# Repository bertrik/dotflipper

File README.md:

# dotflipper
My Flip Dot controller, based on the PCA9865 i2c port expanders

CC BY-SA 4.0

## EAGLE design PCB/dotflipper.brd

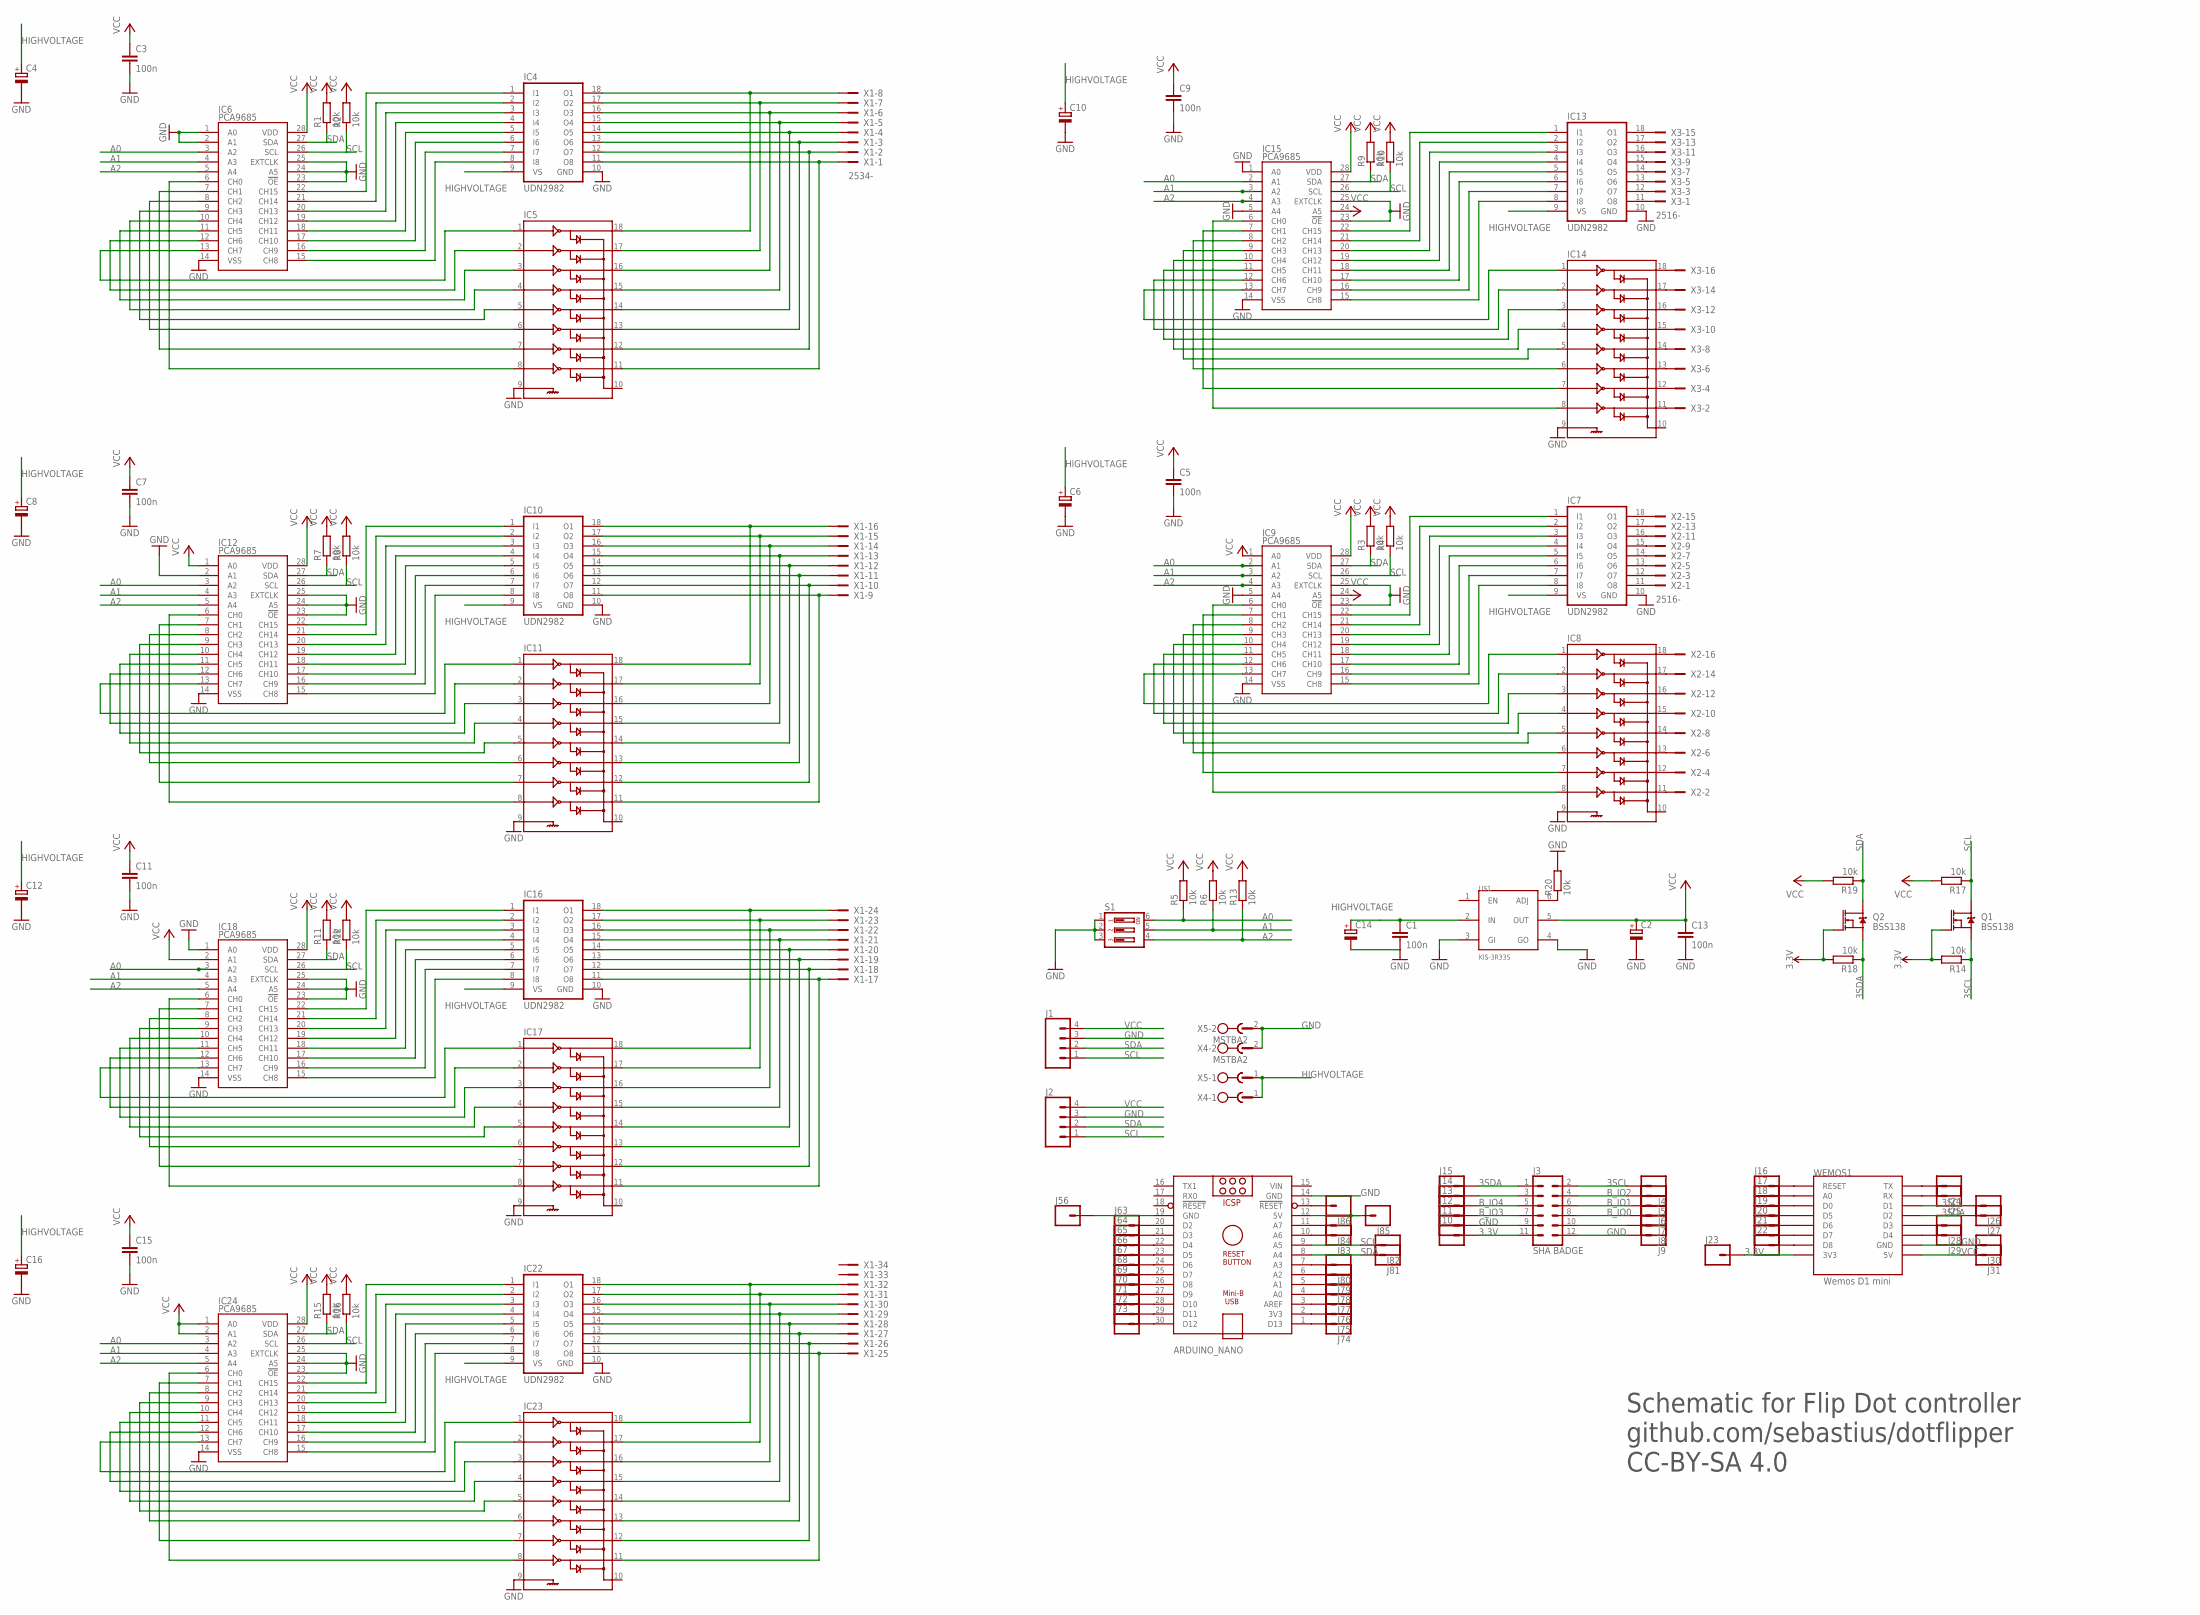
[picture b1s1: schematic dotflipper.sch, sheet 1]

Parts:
ARDUINO_NANO: ARDUINO_NANO
C1, C3, C5, C7, C9, C11, C13, C15: 100n; C0603
C2, C14: CPOL-EUSANYO_SMD_F8; SANYO-OSCON_SMD_F8
C4, C6, C8, C10, C12, C16: CPOL-EUE2.5-6; E2,5-6
IC4, IC7, IC10, IC13, IC16, IC22: UDN2982; DIL18
IC5, IC8, IC11, IC14, IC17, IC23: ULN2803DIP; DIL18
IC6, IC9, IC12, IC15, IC18, IC24: PCA9685; TSSOP-28_4MM
J1, J2: CONN_04; 1X04
J3: SHA BADGE; 2X6
J4, J5, J6, J7, J8, J9, J10, J11, J12, J13, J14, J15, J16, J17, J18, J19, J20, J21, J22, J23, J24, J25, J26, J27, J28, J29, J30, J31, J56, J63, J64, J65, J66, J67, J68, J69, J70, J71, J72, J73, J74, J75, J76, J77, J78, J79, J80, J81, J82, J83, J84, J85, J86: CONN_01; 1X01
Q1, Q2: BSS138; SOT23-3
R1, R2, R3, R4, R5, R6, R7, R8, R9, R10, R11, R12, R13, R14, R15, R16, R17, R18, R19, R20: 10k; R0603
S1: DIP03YL
U$1: KIS-3R33S
WEMOS1: Wemos D1 mini; WEMOS-D1-MINI
X1: 2534-; PAK100/2500-34
X2, X3: 2516-; PAK100/2500-16
X4, X5: MSTBA2

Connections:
3.3V: J3.11, J10.1, J23.1, Q1.1 (G), Q2.1 (G), R14.2, R18.2, WEMOS1.3V3
3SCL: J3.2, J4.1, J26.1, Q1.2 (S), R14.1, WEMOS1.D1
3SDA: J3.1, J15.1, J27.1, Q2.2 (S), R18.1, WEMOS1.D2
A0: IC6.3 (A2), IC9.2 (A1), IC12.3 (A2), IC15.2 (A1), IC18.3 (A2), IC24.3 (A2), R5.1, S1.6
A1: IC6.4 (A3), IC9.3 (A2), IC12.4 (A3), IC15.3 (A2), IC18.4 (A3), IC24.4 (A3), R6.1, S1.5
A2: IC6.5 (A4), IC9.4 (A3), IC12.5 (A4), IC15.4 (A3), IC18.5 (A4), IC24.5 (A4), R13.1, S1.4
B_IO0: J3.8, J7.1
B_IO1: J3.6, J6.1
B_IO2: J3.4, J5.1
B_IO3: J3.7, J12.1
B_IO4: J3.5, J13.1
GND: ARDUINO_NANO.14 (GND), ARDUINO_NANO.19 (GND), C1.2, C2.-, C3.2, C4.-, C5.2, C6.-, C7.2, C8.-, C9.2, C10.-, C11.2, C12.-, C13.2, C14.-, C15.2, C16.-, IC4.10 (GND), IC5.9, IC6.1 (A0), IC6.2 (A1), IC6.14 (VSS), IC6.23 (!OE), IC6.24 (A5), IC6.25 (EXTCLK), IC7.10 (GND), IC8.9, IC9.5 (A4), IC9.14 (VSS), IC9.23 (!OE), IC9.25 (EXTCLK), IC10.10 (GND), IC11.9, IC12.2 (A1), IC12.14 (VSS), IC12.23 (!OE), IC12.24 (A5), IC12.25 (EXTCLK), IC13.10 (GND), IC14.9, IC15.1 (A0), IC15.5 (A4), IC15.14 (VSS), IC15.23 (!OE), IC15.25 (EXTCLK), IC16.10 (GND), IC17.9, IC18.1 (A0), IC18.14 (VSS), IC18.23 (!OE), IC18.24 (A5), IC18.25 (EXTCLK), IC22.10 (GND), IC23.9, IC24.14 (VSS), IC24.23 (!OE), IC24.24 (A5), IC24.25 (EXTCLK), J1.3, J2.3, J3.9, J3.12, J9.1, J11.1, J30.1, J56.1, R20.2, S1.1, S1.2, S1.3, U$1.3 (GI), U$1.4 (GO), WEMOS1.GND, X4.2, X5.2
HIGHVOLTAGE: C1.1, C4.+, C6.+, C8.+, C10.+, C12.+, C14.+, C16.+, IC4.9 (VS), IC7.9 (VS), IC10.9 (VS), IC13.9 (VS), IC16.9 (VS), IC22.9 (VS), U$1.2 (IN), X4.1, X5.1
unnamed: IC4.1 (I1), IC6.22 (CH15)
unnamed: IC4.2 (I2), IC6.21 (CH14)
unnamed: IC4.3 (I3), IC6.20 (CH13)
unnamed: IC4.4 (I4), IC6.19 (CH12)
unnamed: IC7.11 (O8), X2.1
unnamed: IC4.5 (I5), IC6.18 (CH11)
unnamed: IC8.11, X2.2
unnamed: IC7.12 (O7), X2.3
unnamed: IC8.12, X2.4
unnamed: IC7.13 (O6), X2.5
unnamed: IC7.14 (O5), X2.7
unnamed: IC7.15 (O4), X2.9
unnamed: IC7.16 (O3), X2.11
unnamed: IC7.17 (O2), X2.13
unnamed: IC7.18 (O1), X2.15
unnamed: IC8.13, X2.6
unnamed: IC4.6 (I6), IC6.17 (CH10)
unnamed: IC4.7 (I7), IC6.16 (CH9)
unnamed: IC8.14, X2.8
unnamed: IC4.8 (I8), IC6.15 (CH8)
unnamed: IC5.4, IC6.10 (CH4)
unnamed: IC8.15, X2.10
unnamed: IC8.16, X2.12
unnamed: IC8.17, X2.14
unnamed: IC5.6, IC6.8 (CH2)
unnamed: IC5.7, IC6.7 (CH1)
unnamed: IC8.18, X2.16
unnamed: IC5.8, IC6.6 (CH0)
unnamed: IC5.2, IC6.12 (CH6)
unnamed: IC5.3, IC6.11 (CH5)
unnamed: IC5.5, IC6.9 (CH3)
unnamed: IC5.1, IC6.13 (CH7)
unnamed: IC13.11 (O8), X3.1
unnamed: IC4.12 (O7), IC5.12, X1.2
unnamed: IC13.12 (O7), X3.3
unnamed: IC4.14 (O5), IC5.14, X1.4
unnamed: IC13.13 (O6), X3.5
unnamed: IC4.16 (O3), IC5.16, X1.6
unnamed: IC13.14 (O5), X3.7
unnamed: IC13.15 (O4), X3.9
unnamed: IC4.18 (O1), IC5.18, X1.8
unnamed: IC13.16 (O3), X3.11
unnamed: IC4.11 (O8), IC5.11, X1.1
unnamed: IC13.17 (O2), X3.13
unnamed: IC4.13 (O6), IC5.13, X1.3
unnamed: IC13.18 (O1), X3.15
unnamed: IC4.15 (O4), IC5.15, X1.5
unnamed: IC4.17 (O2), IC5.17, X1.7
unnamed: IC7.1 (I1), IC9.22 (CH15)
unnamed: IC7.2 (I2), IC9.21 (CH14)
unnamed: IC7.3 (I3), IC9.20 (CH13)
unnamed: IC7.4 (I4), IC9.19 (CH12)
unnamed: IC7.5 (I5), IC9.18 (CH11)
unnamed: IC7.6 (I6), IC9.17 (CH10)
unnamed: IC7.7 (I7), IC9.16 (CH9)
unnamed: IC7.8 (I8), IC9.15 (CH8)
unnamed: IC8.4, IC9.10 (CH4)
unnamed: IC8.6, IC9.8 (CH2)
unnamed: IC8.7, IC9.7 (CH1)
unnamed: IC8.8, IC9.6 (CH0)
unnamed: IC8.2, IC9.12 (CH6)
unnamed: IC8.3, IC9.11 (CH5)
unnamed: IC8.5, IC9.9 (CH3)
unnamed: IC8.1, IC9.13 (CH7)
unnamed: IC14.11, X3.2
unnamed: IC14.12, X3.4
unnamed: IC14.13, X3.6
unnamed: IC14.14, X3.8
unnamed: IC14.15, X3.10
unnamed: IC14.16, X3.12
unnamed: IC14.17, X3.14
unnamed: IC14.18, X3.16
unnamed: IC10.1 (I1), IC12.22 (CH15)
unnamed: IC10.2 (I2), IC12.21 (CH14)
unnamed: IC10.3 (I3), IC12.20 (CH13)
unnamed: IC10.4 (I4), IC12.19 (CH12)
unnamed: IC10.5 (I5), IC12.18 (CH11)
unnamed: IC10.6 (I6), IC12.17 (CH10)
unnamed: IC10.7 (I7), IC12.16 (CH9)
unnamed: IC10.8 (I8), IC12.15 (CH8)
unnamed: IC11.4, IC12.10 (CH4)
unnamed: IC11.6, IC12.8 (CH2)
unnamed: IC11.7, IC12.7 (CH1)
unnamed: IC11.8, IC12.6 (CH0)
unnamed: IC11.2, IC12.12 (CH6)
unnamed: IC11.3, IC12.11 (CH5)
unnamed: IC11.5, IC12.9 (CH3)
unnamed: IC11.1, IC12.13 (CH7)
unnamed: IC10.12 (O7), IC11.12, X1.10
unnamed: IC10.14 (O5), IC11.14, X1.12
unnamed: IC10.16 (O3), IC11.16, X1.14
unnamed: IC10.18 (O1), IC11.18, X1.16
unnamed: IC10.11 (O8), IC11.11, X1.9
unnamed: IC10.13 (O6), IC11.13, X1.11
unnamed: IC10.15 (O4), IC11.15, X1.13
unnamed: IC10.17 (O2), IC11.17, X1.15
unnamed: J16.1, WEMOS1.RESET
unnamed: J17.1, WEMOS1.A0
unnamed: J3.3, J14.1
unnamed: R20.1, U$1.6 (ADJ)
unnamed: J18.1, WEMOS1.D0
unnamed: J19.1, WEMOS1.D5
unnamed: J20.1, WEMOS1.D6
unnamed: J21.1, WEMOS1.D7
unnamed: IC13.1 (I1), IC15.22 (CH15)
unnamed: IC13.2 (I2), IC15.21 (CH14)
unnamed: IC13.3 (I3), IC15.20 (CH13)
unnamed: IC13.4 (I4), IC15.19 (CH12)
unnamed: IC13.5 (I5), IC15.18 (CH11)
unnamed: IC13.6 (I6), IC15.17 (CH10)
unnamed: IC13.7 (I7), IC15.16 (CH9)
unnamed: IC13.8 (I8), IC15.15 (CH8)
unnamed: IC14.4, IC15.10 (CH4)
unnamed: IC14.6, IC15.8 (CH2)
unnamed: IC14.7, IC15.7 (CH1)
unnamed: IC14.8, IC15.6 (CH0)
unnamed: IC14.2, IC15.12 (CH6)
unnamed: IC14.3, IC15.11 (CH5)
unnamed: IC14.5, IC15.9 (CH3)
unnamed: IC14.1, IC15.13 (CH7)
unnamed: IC16.1 (I1), IC18.22 (CH15)
unnamed: IC16.2 (I2), IC18.21 (CH14)
unnamed: IC16.3 (I3), IC18.20 (CH13)
unnamed: IC16.4 (I4), IC18.19 (CH12)
unnamed: IC16.5 (I5), IC18.18 (CH11)
unnamed: IC16.6 (I6), IC18.17 (CH10)
unnamed: IC16.7 (I7), IC18.16 (CH9)
unnamed: IC16.8 (I8), IC18.15 (CH8)
unnamed: IC17.4, IC18.10 (CH4)
unnamed: IC17.6, IC18.8 (CH2)
unnamed: IC17.7, IC18.7 (CH1)
unnamed: IC17.8, IC18.6 (CH0)
unnamed: IC17.2, IC18.12 (CH6)
unnamed: IC17.3, IC18.11 (CH5)
unnamed: IC17.5, IC18.9 (CH3)
unnamed: IC17.1, IC18.13 (CH7)
unnamed: IC16.12 (O7), IC17.12, X1.18
unnamed: IC16.14 (O5), IC17.14, X1.20
unnamed: IC16.16 (O3), IC17.16, X1.22
unnamed: IC16.18 (O1), IC17.18, X1.24
unnamed: IC16.11 (O8), IC17.11, X1.17
unnamed: IC16.13 (O6), IC17.13, X1.19
unnamed: IC16.15 (O4), IC17.15, X1.21
unnamed: IC16.17 (O2), IC17.17, X1.23
unnamed: J22.1, WEMOS1.D8
unnamed: J24.1, WEMOS1.TX
unnamed: J3.10, J8.1
unnamed: J25.1, WEMOS1.RX
unnamed: J28.1, WEMOS1.D3
unnamed: J29.1, WEMOS1.D4
unnamed: ARDUINO_NANO.20 (D2), J63.1
unnamed: ARDUINO_NANO.21 (D3), J64.1
unnamed: ARDUINO_NANO.22 (D4), J65.1
unnamed: ARDUINO_NANO.23 (D5), J66.1
unnamed: ARDUINO_NANO.24 (D6), J67.1
unnamed: ARDUINO_NANO.25 (D7), J68.1
unnamed: ARDUINO_NANO.26 (D8), J69.1
unnamed: ARDUINO_NANO.27 (D9), J70.1
unnamed: ARDUINO_NANO.28 (D10), J71.1
unnamed: ARDUINO_NANO.29 (D11), J72.1
unnamed: ARDUINO_NANO.30 (D12), J73.1
unnamed: ARDUINO_NANO.1 (D13), J74.1
unnamed: ARDUINO_NANO.2 (3V3), J75.1
unnamed: ARDUINO_NANO.3 (AREF), J76.1
unnamed: ARDUINO_NANO.4 (A0), J77.1
unnamed: ARDUINO_NANO.5 (A1), J78.1
unnamed: ARDUINO_NANO.6 (A2), J79.1
unnamed: IC22.1 (I1), IC24.22 (CH15)
unnamed: IC22.2 (I2), IC24.21 (CH14)
unnamed: IC22.3 (I3), IC24.20 (CH13)
unnamed: IC22.4 (I4), IC24.19 (CH12)
unnamed: IC22.5 (I5), IC24.18 (CH11)
unnamed: IC22.6 (I6), IC24.17 (CH10)
unnamed: IC22.7 (I7), IC24.16 (CH9)
unnamed: IC22.8 (I8), IC24.15 (CH8)
unnamed: IC23.4, IC24.10 (CH4)
unnamed: IC23.6, IC24.8 (CH2)
unnamed: IC23.7, IC24.7 (CH1)
unnamed: IC23.8, IC24.6 (CH0)
unnamed: IC23.2, IC24.12 (CH6)
unnamed: IC23.3, IC24.11 (CH5)
unnamed: IC23.5, IC24.9 (CH3)
unnamed: IC23.1, IC24.13 (CH7)
unnamed: IC22.12 (O7), IC23.12, X1.26
unnamed: IC22.14 (O5), IC23.14, X1.28
unnamed: IC22.16 (O3), IC23.16, X1.30
unnamed: IC22.18 (O1), IC23.18, X1.32
unnamed: IC22.11 (O8), IC23.11, X1.25
unnamed: IC22.13 (O6), IC23.13, X1.27
unnamed: IC22.15 (O4), IC23.15, X1.29
unnamed: IC22.17 (O2), IC23.17, X1.31
unnamed: ARDUINO_NANO.7 (A3), J80.1
unnamed: ARDUINO_NANO.10 (A6), J83.1
unnamed: ARDUINO_NANO.11 (A7), J84.1
unnamed: ARDUINO_NANO.13 (!RESET), J86.1
SCL: ARDUINO_NANO.9 (A5), IC6.26 (SCL), IC9.26 (SCL), IC12.26 (SCL), IC15.26 (SCL), IC18.26 (SCL), IC24.26 (SCL), J1.1, J2.1, J82.1, Q1.3 (D), R2.1, R4.1, R8.1, R10.1, R12.1, R16.1, R17.1
SDA: ARDUINO_NANO.8 (A4), IC6.27 (SDA), IC9.27 (SDA), IC12.27 (SDA), IC15.27 (SDA), IC18.27 (SDA), IC24.27 (SDA), J1.2, J2.2, J81.1, Q2.3 (D), R1.1, R3.1, R7.1, R9.1, R11.1, R15.1, R19.1
VCC: ARDUINO_NANO.12 (5V), C2.+, C3.1, C5.1, C7.1, C9.1, C11.1, C13.1, C15.1, IC6.28 (VDD), IC9.1 (A0), IC9.24 (A5), IC9.28 (VDD), IC12.1 (A0), IC12.28 (VDD), IC15.24 (A5), IC15.28 (VDD), IC18.2 (A1), IC18.28 (VDD), IC24.1 (A0), IC24.2 (A1), IC24.28 (VDD), J1.4, J2.4, J31.1, J85.1, R1.2, R2.2, R3.2, R4.2, R5.2, R6.2, R7.2, R8.2, R9.2, R10.2, R11.2, R12.2, R13.2, R15.2, R16.2, R17.2, R19.2, U$1.5 (OUT), WEMOS1.5V
VIN: ARDUINO_NANO.15 (VIN)

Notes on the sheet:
Schematic for Flip Dot controller github.com/sebastius/dotflipper CC-BY-SA 4.0

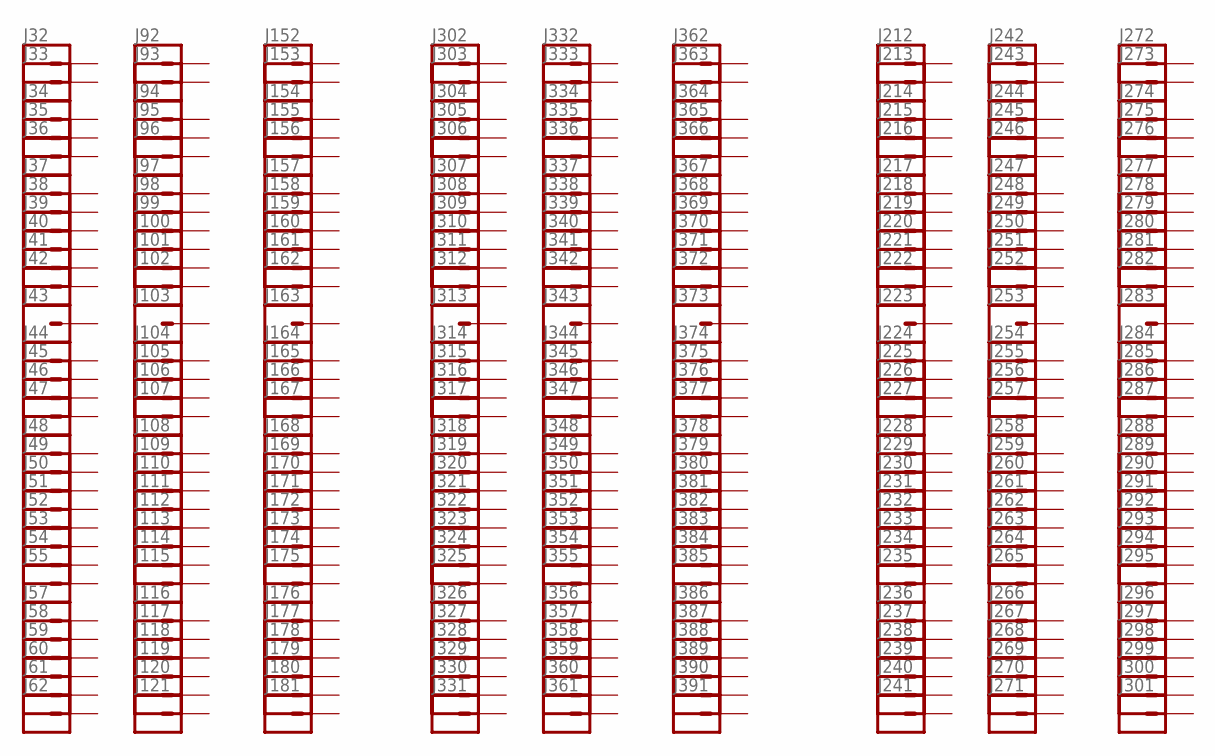
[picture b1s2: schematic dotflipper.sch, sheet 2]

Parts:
J32, J33, J34, J35, J36, J37, J38, J39, J40, J41, J42, J43, J44, J45, J46, J47, J48, J49, J50, J51, J52, J53, J54, J55, J57, J58, J59, J60, J61, J62, J92, J93, J94, J95, J96, J97, J98, J99, J100, J101, J102, J103, J104, J105, J106, J107, J108, J109, J110, J111, J112, J113, J114, J115, J116, J117, J118, J119, J120, J121, J152, J153, J154, J155, J156, J157, J158, J159, J160, J161, J162, J163, J164, J165, J166, J167, J168, J169, J170, J171, J172, J173, J174, J175, J176, J177, J178, J179, J180, J181, J212, J213, J214, J215, J216, J217, J218, J219, J220, J221, J222, J223, J224, J225, J226, J227, J228, J229, J230, J231, J232, J233, J234, J235, J236, J237, J238, J239, J240, J241, J242, J243, J244, J245, J246, J247, J248, J249, J250, J251, J252, J253, J254, J255, J256, J257, J258, J259, J260, J261, J262, J263, J264, J265, J266, J267, J268, J269, J270, J271, J272, J273, J274, J275, J276, J277, J278, J279, J280, J281, J282, J283, J284, J285, J286, J287, J288, J289, J290, J291, J292, J293, J294, J295, J296, J297, J298, J299, J300, J301, J302, J303, J304, J305, J306, J307, J308, J309, J310, J311, J312, J313, J314, J315, J316, J317, J318, J319, J320, J321, J322, J323, J324, J325, J326, J327, J328, J329, J330, J331, J332, J333, J334, J335, J336, J337, J338, J339, J340, J341, J342, J343, J344, J345, J346, J347, J348, J349, J350, J351, J352, J353, J354, J355, J356, J357, J358, J359, J360, J361, J362, J363, J364, J365, J366, J367, J368, J369, J370, J371, J372, J373, J374, J375, J376, J377, J378, J379, J380, J381, J382, J383, J384, J385, J386, J387, J388, J389, J390, J391: CONN_01; 1X01

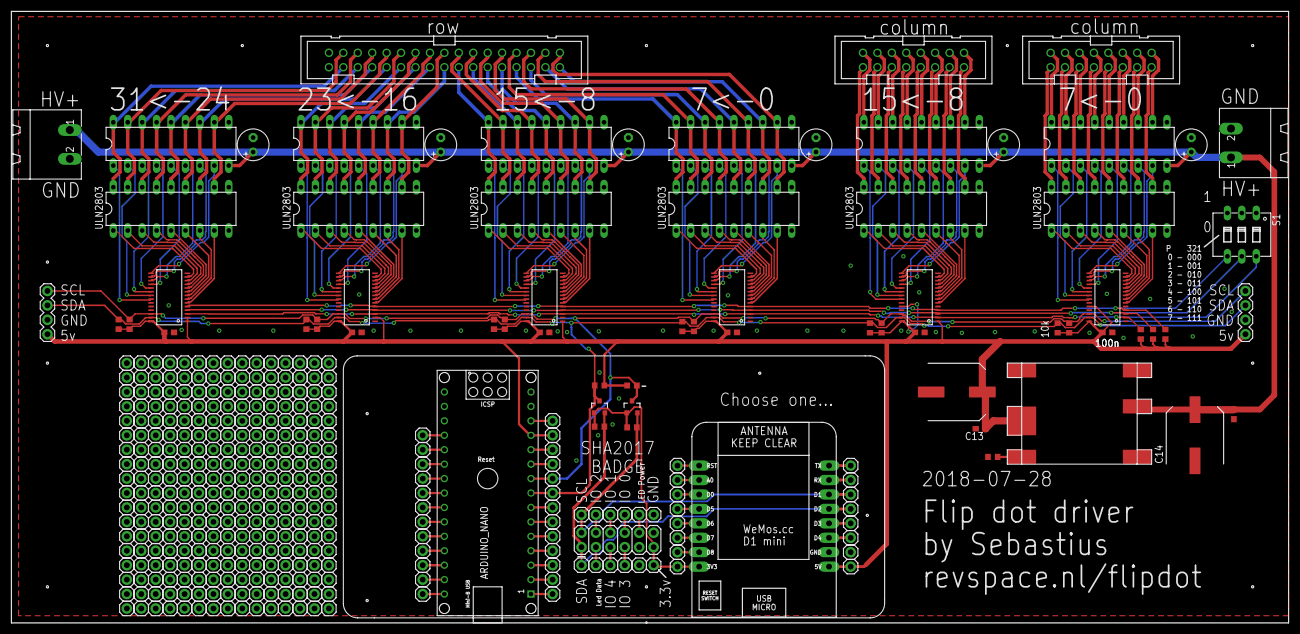
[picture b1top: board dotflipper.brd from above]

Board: 2 copper layers, 224.8 x 107.6 mm, 391 parts (0 on the bottom side), 211 nets.

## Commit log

2018-07-29 First public release
2018-07-29 typo
2018-07-29 fuck icloud
2018-07-30 Readability and more explanation of how to flip a bit based on boolean color
2018-07-30 Minor cleanup of schematic. Made PDFs for those without Eagle.
2018-08-08 Extra beveligingen ingebouwd Code netter gemaakt (vind ik) Ik kan nog steeds niet mooie commitmessages maken
2018-08-08 adress -> address
2018-08-08 added units to defines, did a little less ternary for improved readability, thanks Joepie91 and Smeding
2018-08-08 More nitpicking to improve readabilty and prevent stupid errors
2018-08-08 ik mag van Eightdot geen strings concatenaten :'(
2018-08-08 Game of Life added
2018-08-08 added a few experiments in screen wipes to the main loop
2018-08-11 Beetje zitten rommelen met effectjes bedenken
2018-08-11 updated safety in void flipdot()
2018-09-01 SNAKES NOT ON A PLANE
2018-09-01 stomme time rename naar mytime
2018-09-02 twee variabelen die niet gebruikt werden weg. Verplaatsen uitlezen joystick naar eigen void. Nog niet af.
2019-05-17 nu incl UDP
2019-05-17 Show the IP address on the matrix when connected
2019-05-17 tetris begint
2019-05-18 tetris werkend

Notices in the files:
parts and their libraries:
SparkFun-IC-Special-Function: Licensing: Creative Commons ShareAlike 4.0 International - https://creativecommons.org/licenses/by-sa/4.0
